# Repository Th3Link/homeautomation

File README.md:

# homeautomation

Components for a CAN-bus home-automation system: relay/rollershutter/
light/button/sensor nodes on a shared CAN bus, bridged to MQTT (and from
there to openHAB or Home Assistant) by a gateway. This repository holds
the hardware (KiCad), mechanics (3D-printable enclosures), and firmware
for the whole system.

**Start here:** [`docs/index.md`](docs/index.md) — the full documentation
index (requirements, architecture decisions, protocol specs), also built
into every crate's `cargo doc` output and published to GitHub Pages.

## Software

The firmware is Rust (`#![no_std]`, [embassy](https://embassy.dev/) async,
[esp-hal](https://github.com/esp-rs/esp-hal)), organized as one Cargo
workspace under `software/`:

- [`common-core`](software/common-core) / [`common-hardware`](software/common-hardware)
  — CAN wire-format types and ESP32 hardware-support helpers shared by
  both firmware lines.
- [`gateway-core`](software/gateway-core) / [`gateway-hardware`](software/gateway-hardware)
  — the CAN↔MQTT bridge: web config UI, `/control.json` RPC, self- and
  CAN-bus OTA update, over wired Ethernet (DHCPv4 + SLAAC, no WiFi).
- [`cancomponents-core`](software/cancomponents-core) / [`cancomponents-hardware`](software/cancomponents-hardware)
  — the node firmware living on the bus: relays, rollershutters, buttons,
  lights.
- [`tools/mqtt-log-reader`](software/tools/mqtt-log-reader) — a small
  Python tool for reading back the gateway's MQTT log/debug topics.
- [`sim/`](software/sim) — `./sim up`: the unchanged gateway and node
  firmware in QEMU, several gateways with their nodes on virtual CAN buses;
  press buttons, set what the sensors measure, watch relays and frames, in
  a TUI, from Python scripts or in pytest.
- [`legacy/`](software/legacy) — the original C++/ESP-IDF implementation,
  kept for reference. No longer built by CI.

### Building

The `*-core` crates are hardware-independent and build/test on any
machine with stable Rust:

```bash
cargo test -p gateway-core -p cancomponents-core -p common-core
```

The `*-hardware` crates target Xtensa (ESP32) and need Espressif's Rust
toolchain fork, installed via [`espup`](https://github.com/esp-rs/espup):

```bash
cargo install espup
espup install
source "$HOME/export-esp.sh"   # needed once per new shell
```

Then, from a `*-hardware` crate directory (e.g. `software/gateway-hardware/`):

```bash
cargo run --release
```

`cargo run` flashes over USB serial and opens a monitor, via `espflash`
(configured as each crate's custom runner in its own `.cargo/config.toml`).

## Hardware

### Relais

Disclaimer: if you put mains voltage on a relais board, make sure you
know what you are doing. These components are experimental and you are in
charge of your own actions. Be safe — if you're unsure, get an expert or
leave it.

Three PCBs, one shared firmware, to switch power on and off:

- **Solid-state relais (SSR)** — mains voltage only (~230V @ 50-60Hz), up
  to 1A per relay, six relais sharing one 1A fuse. Be careful with
  capacitive/inductive loads; handles small rollershutters, heating
  actuators, and electro-magnetic contactors fine.
- **Regular relais** — up to 16A each, no on-board fuse (protect your own
  circuits). No arc-quenching chamber, so an electro-magnetic contactor is
  a better choice for heavy inductive loads (motors, frequency drives).
- **Rollershutter** — two cascaded relais per channel (power, then
  up/down), with software interlocking so up and down are never active
  at once.

All three use the same firmware and the same ESP32 pinning, and each has
one extension port for up to 4 additional relay or sensor boards.

### Lightswitch, sensors, CAN header/hub, UART adapter

Additional boards in `hardware/` — see each board's own KiCad project for
details; written documentation for these is still a work in progress.

## CAN bus and MQTT protocol

See [`docs/protocol-can.md`](docs/protocol-can.md) for the byte-level CAN
wire format shared by every component, and
[`software/gateway-core/docs/protocol-mqtt.md`](software/gateway-core/docs/protocol-mqtt.md)
for the gateway's MQTT topic scheme. (Extension-board channel/button
numbering conventions used by the node firmware — e.g. which CAN
`NO`/button-id ranges map to which extension address — are documented at
the node firmware level; `docs/protocol-can.md` covers the CAN frame
format itself.)

## CI

- **CI** — `cargo fmt` / `cargo clippy` for every crate, `cargo nextest`
  with coverage and an MSRV check for the `*-core` crates.
- **Docs** — `cargo doc` for every crate, published to GitHub Pages.
- **Security audit** — [`cargo-audit`](https://github.com/rustsec/rustsec)
  against the RustSec advisory database, on every dependency change and
  once daily.
- **Renovate** — automated dependency-update PRs, once daily.

`software/legacy/` (the original C++/ESP-IDF code) is no longer built by
CI — see its own `README.md` for the ESP-IDF build steps if you need to
reproduce it.

## License

GNU General Public License v3.0 (or later) — see [LICENSE](LICENSE).

This is meant to be freely buildable, flashable, and modifiable hardware
and firmware. GPLv3 was chosen deliberately: its copyleft means anything
built on this stays open, and its Section 6 "Installation Information"
requirement means anyone who conveys a modified version as part of a
physical product also has to provide what's needed to install your own
modified firmware on it — nobody gets to lock you out of hardware you own.
All schematics, layouts, mechanics, tools, and software are provided so
you can fix things yourself rather than throwing them away.

## Contribution

Feel free to report issues or open a pull request.

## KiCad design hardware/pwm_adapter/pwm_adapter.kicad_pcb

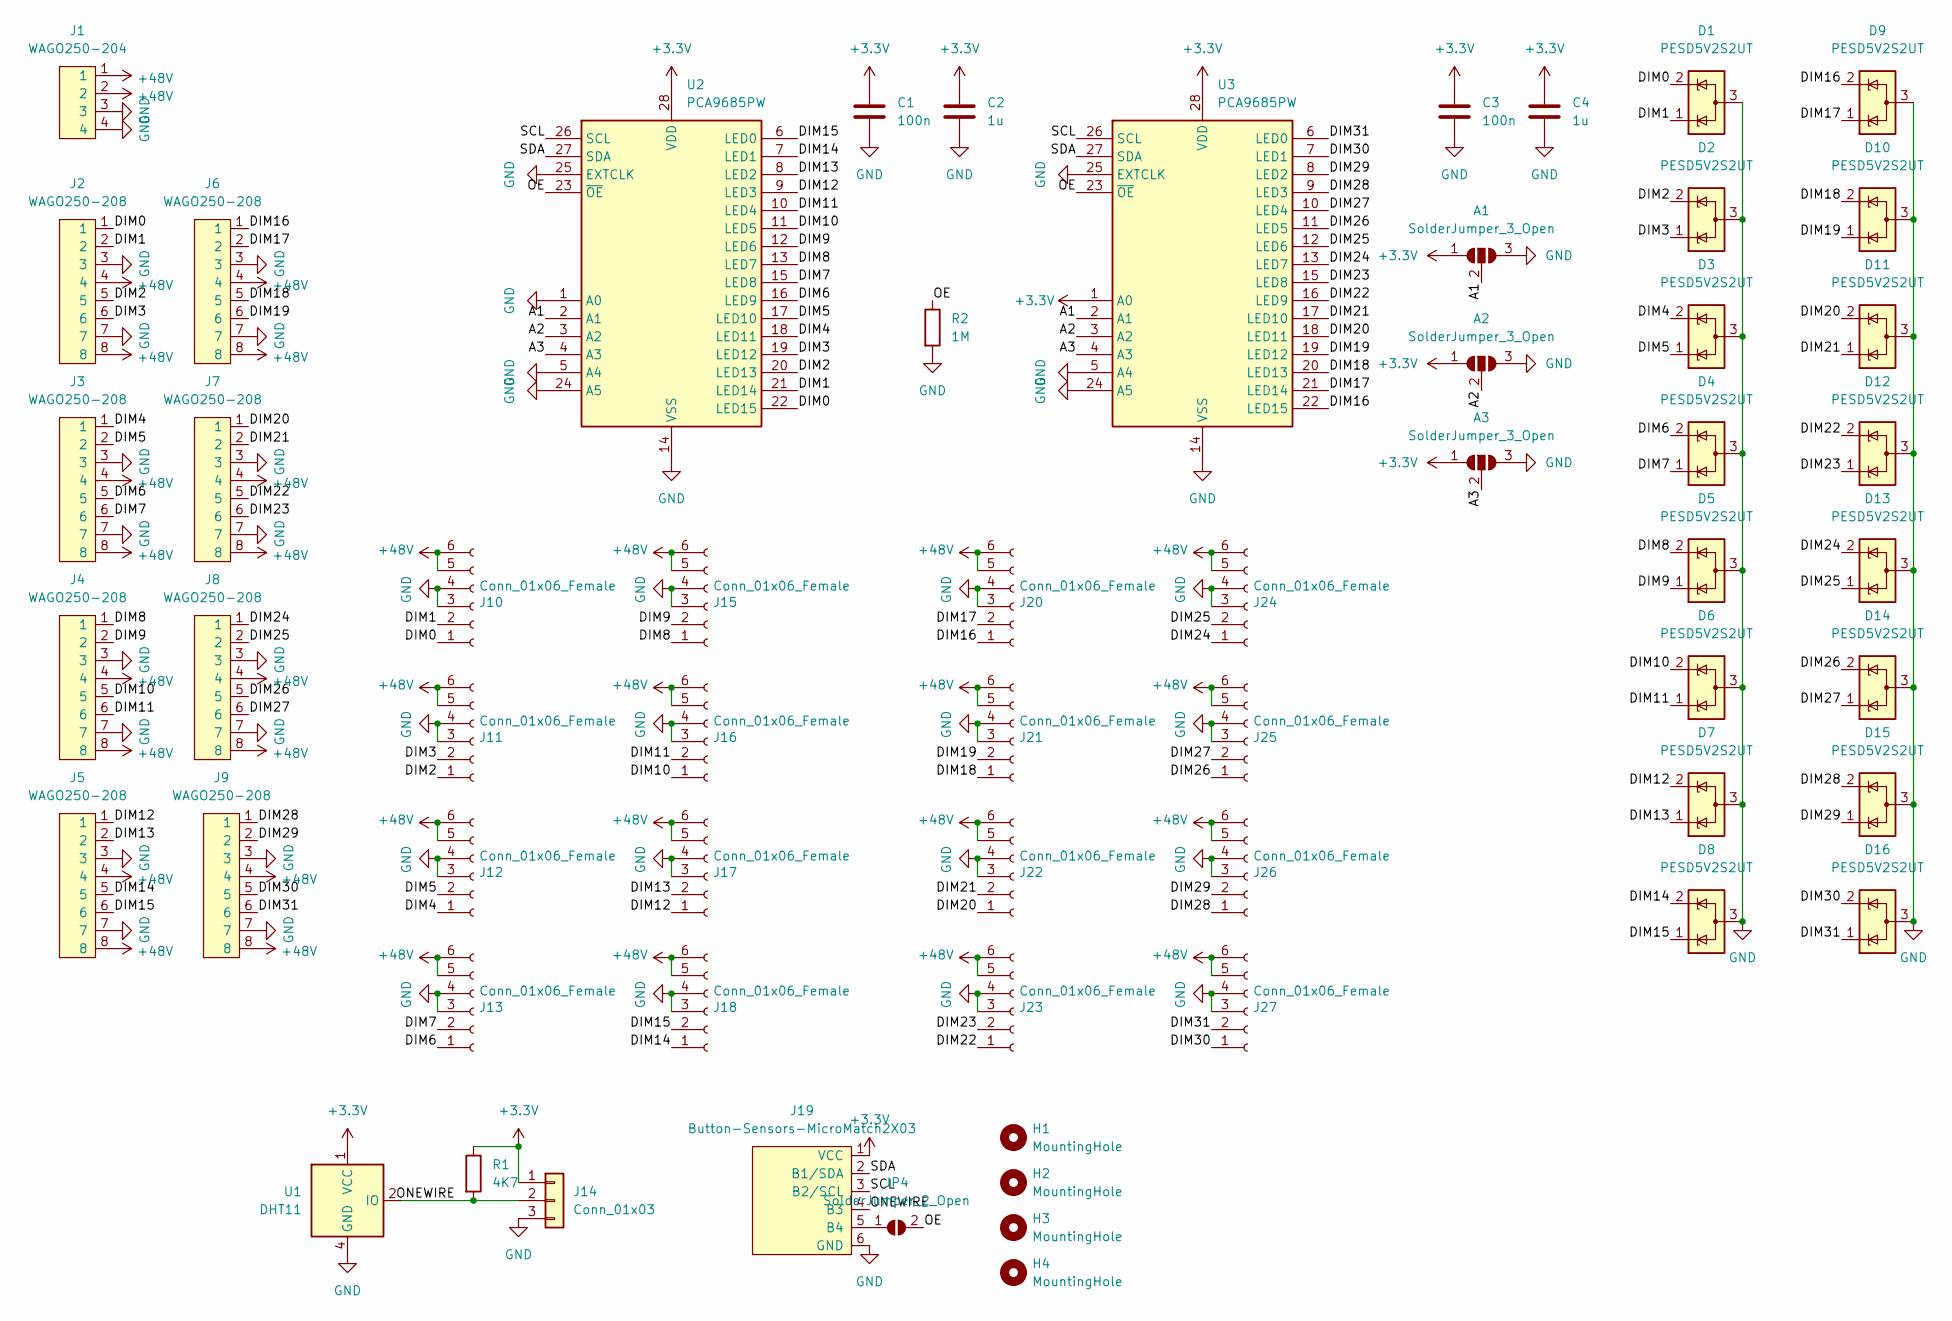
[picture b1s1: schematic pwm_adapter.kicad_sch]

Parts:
A1, A2, A3: SolderJumper_3_Open; SolderJumper-3_P1.3mm_Open_RoundedPad1.0x1.5mm
C1, C3: 100n; C_0603_1608Metric_Pad1.08x0.95mm_HandSolder
C2, C4: 1u; C_0603_1608Metric_Pad1.08x0.95mm_HandSolder
D1, D2, D3, D4, D5, D6, D7, D8, D9, D10, D11, D12, D13, D14, D15, D16: PESD5V2S2UT; SOT-23
H1, H2, H3, H4: MountingHole; MountingHole_4.3mm_M4_DIN965
J1: WAGO250-204
J2, J3, J4, J5, J6, J7, J8, J9: WAGO250-208
J10, J11, J12, J13, J15, J16, J17, J18, J20, J21, J22, J23, J24, J25, J26, J27: Conn_01x06_Female; 02x03MicroMatch
J14: Conn_01x03; PinHeader_1x03_P2.54mm_Vertical
J19: Button-Sensors-MicroMatch2X03; 02x03MicroMatch
JP4: SolderJumper_2_Open; SolderJumper-2_P1.3mm_Open_RoundedPad1.0x1.5mm
R1: 4K7; R_0603_1608Metric_Pad0.98x0.95mm_HandSolder
R2: 1M; R_0603_1608Metric_Pad0.98x0.95mm_HandSolder
U1: DHT11; Aosong_DHT11_5.5x12.0_P2.54mm
U2, U3: PCA9685PW; TSSOP-28_4.4x9.7mm_P0.65mm

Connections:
+3.3V: A1.1 (A), A2.1 (A), A3.1 (A), C1.1, C2.1, C3.1, C4.1, J14.1, J19.1 (VCC), R1.1, U1.1 (VCC), U2.28 (VDD), U3.1 (A0), U3.28 (VDD)
+48V: J1.1, J1.2, J2.4, J2.8, J3.4, J3.8, J4.4, J4.8, J5.4, J5.8, J6.4, J6.8, J7.4, J7.8, J8.4, J8.8, J9.4, J9.8, J10.5, J10.6, J11.5, J11.6, J12.5, J12.6, J13.5, J13.6, J15.5, J15.6, J16.5, J16.6, J17.5, J17.6, J18.5, J18.6, J20.5, J20.6, J21.5, J21.6, J22.5, J22.6, J23.5, J23.6, J24.5, J24.6, J25.5, J25.6, J26.5, J26.6, J27.5, J27.6
/A1: A1.2 (C), U2.2 (A1), U3.2 (A1)
/A2: A2.2 (C), U2.3 (A2), U3.3 (A2)
/A3: A3.2 (C), U2.4 (A3), U3.4 (A3)
/DIM0: D1.2 (K), J2.1, J10.1, U2.22 (LED15)
/DIM1: D1.1 (K), J2.2, J10.2, U2.21 (LED14)
/DIM2: D2.2 (K), J2.5, J11.1, U2.20 (LED13)
/DIM3: D2.1 (K), J2.6, J11.2, U2.19 (LED12)
/DIM4: D3.2 (K), J3.1, J12.1, U2.18 (LED11)
/DIM5: D3.1 (K), J3.2, J12.2, U2.17 (LED10)
/DIM6: D4.2 (K), J3.5, J13.1, U2.16 (LED9)
/DIM7: D4.1 (K), J3.6, J13.2, U2.15 (LED8)
/DIM8: D5.2 (K), J4.1, J15.1, U2.13 (LED7)
/DIM9: D5.1 (K), J4.2, J15.2, U2.12 (LED6)
/DIM10: D6.2 (K), J4.5, J16.1, U2.11 (LED5)
/DIM11: D6.1 (K), J4.6, J16.2, U2.10 (LED4)
/DIM12: D7.2 (K), J5.1, J17.1, U2.9 (LED3)
/DIM13: D7.1 (K), J5.2, J17.2, U2.8 (LED2)
/DIM14: D8.2 (K), J5.5, J18.1, U2.7 (LED1)
/DIM15: D8.1 (K), J5.6, J18.2, U2.6 (LED0)
/DIM16: D9.2 (K), J6.1, J20.1, U3.22 (LED15)
/DIM17: D9.1 (K), J6.2, J20.2, U3.21 (LED14)
/DIM18: D10.2 (K), J6.5, J21.1, U3.20 (LED13)
/DIM19: D10.1 (K), J6.6, J21.2, U3.19 (LED12)
/DIM20: D11.2 (K), J7.1, J22.1, U3.18 (LED11)
/DIM21: D11.1 (K), J7.2, J22.2, U3.17 (LED10)
/DIM22: D12.2 (K), J7.5, J23.1, U3.16 (LED9)
/DIM23: D12.1 (K), J7.6, J23.2, U3.15 (LED8)
/DIM24: D13.2 (K), J8.1, J24.1, U3.13 (LED7)
/DIM25: D13.1 (K), J8.2, J24.2, U3.12 (LED6)
/DIM26: D14.2 (K), J8.5, J25.1, U3.11 (LED5)
/DIM27: D14.1 (K), J8.6, J25.2, U3.10 (LED4)
/DIM28: D15.2 (K), J9.1, J26.1, U3.9 (LED3)
/DIM29: D15.1 (K), J9.2, J26.2, U3.8 (LED2)
/DIM30: D16.2 (K), J9.5, J27.1, U3.7 (LED1)
/DIM31: D16.1 (K), J9.6, J27.2, U3.6 (LED0)
/OE: JP4.2 (B), R2.1, U2.23 (~OE), U3.23 (~OE)
/ONEWIRE: J14.2, J19.4 (B3), R1.2, U1.2 (IO)
/SCL: J19.3 (B2/SCL), U2.26 (SCL), U3.26 (SCL)
/SDA: J19.2 (B1/SDA), U2.27 (SDA), U3.27 (SDA)
GND: A1.3 (B), A2.3 (B), A3.3 (B), C1.2, C2.2, C3.2, C4.2, D1.3 (A), D2.3 (A), D3.3 (A), D4.3 (A), D5.3 (A), D6.3 (A), D7.3 (A), D8.3 (A), D9.3 (A), D10.3 (A), D11.3 (A), D12.3 (A), D13.3 (A), D14.3 (A), D15.3 (A), D16.3 (A), J1.3, J1.4, J2.3, J2.7, J3.3, J3.7, J4.3, J4.7, J5.3, J5.7, J6.3, J6.7, J7.3, J7.7, J8.3, J8.7, J9.3, J9.7, J10.3, J10.4, J11.3, J11.4, J12.3, J12.4, J13.3, J13.4, J14.3, J15.3, J15.4, J16.3, J16.4, J17.3, J17.4, J18.3, J18.4, J19.6 (GND), J20.3, J20.4, J21.3, J21.4, J22.3, J22.4, J23.3, J23.4, J24.3, J24.4, J25.3, J25.4, J26.3, J26.4, J27.3, J27.4, R2.2, U1.4 (GND), U2.1 (A0), U2.5 (A4), U2.14 (VSS), U2.24 (A5), U2.25 (EXTCLK), U3.5 (A4), U3.14 (VSS), U3.24 (A5), U3.25 (EXTCLK)
unnamed: J19.5 (B4), JP4.1 (A)

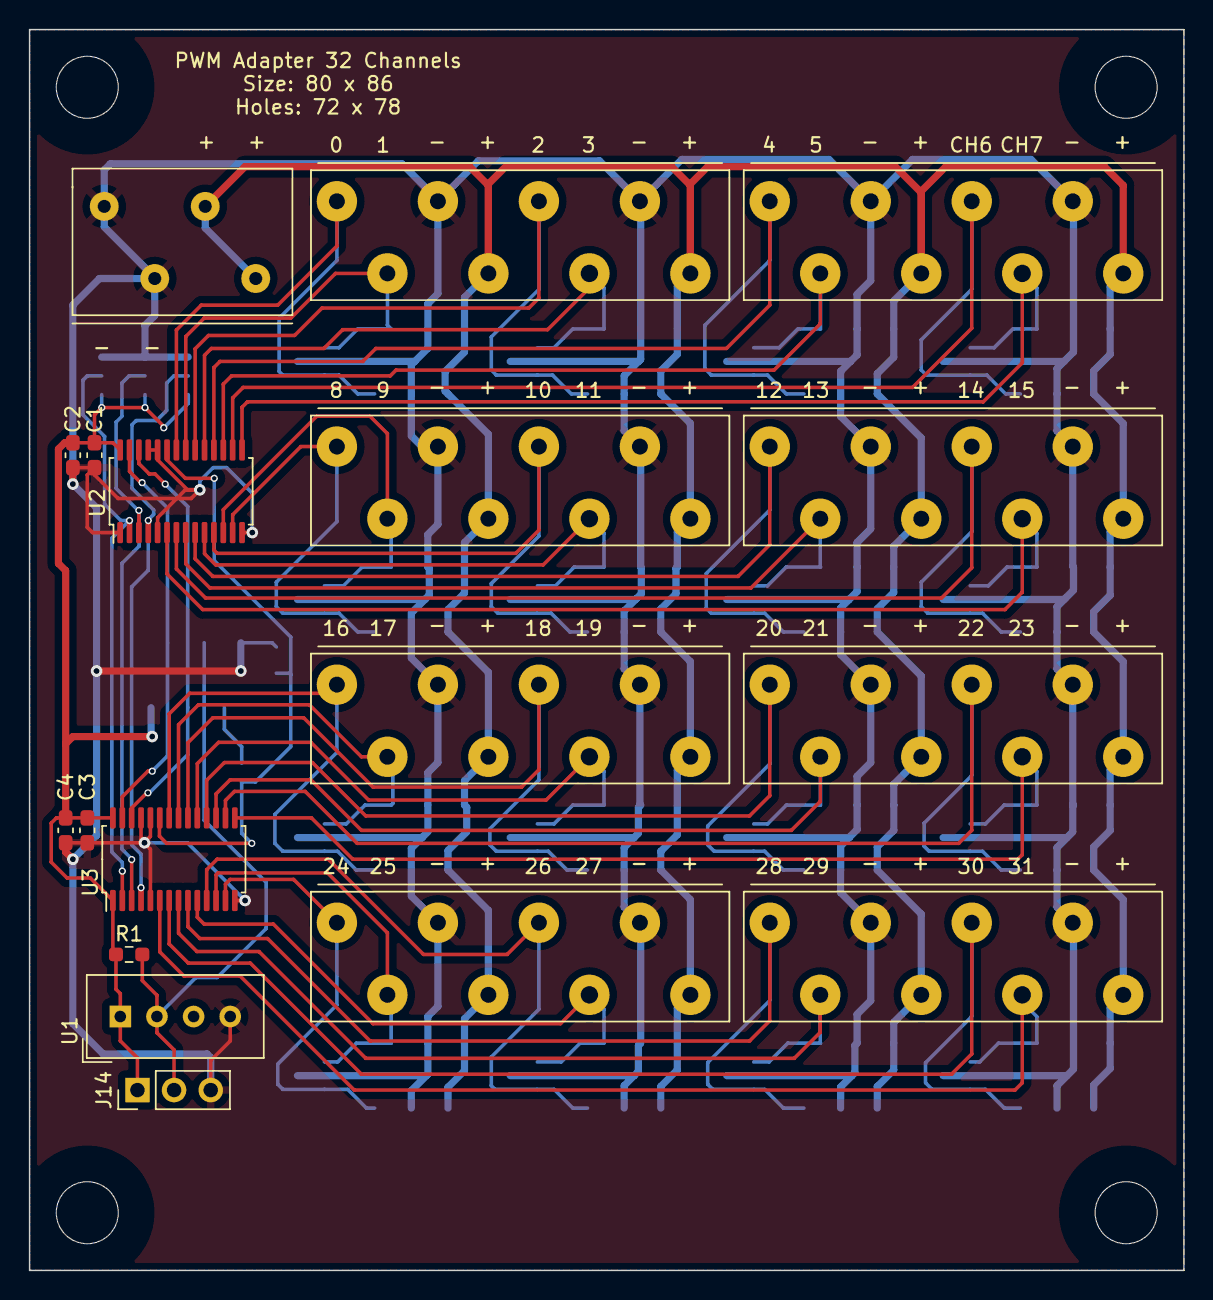
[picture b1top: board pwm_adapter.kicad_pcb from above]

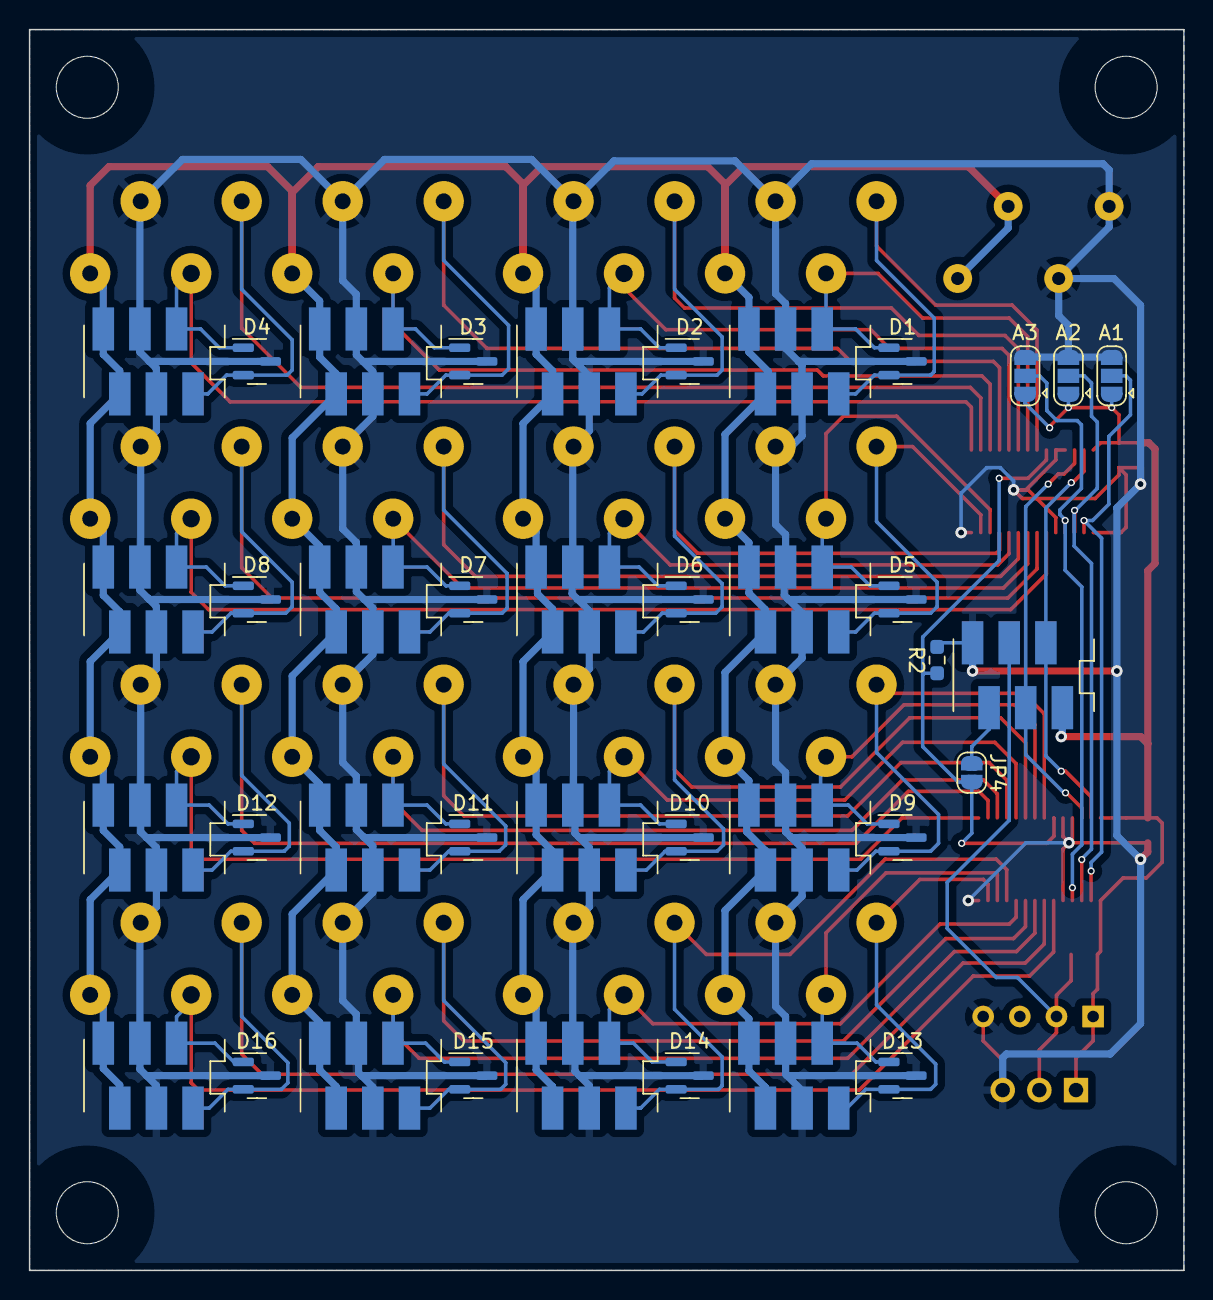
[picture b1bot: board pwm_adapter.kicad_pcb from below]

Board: 2 copper layers, 80.0 x 86.0 mm, 60 parts (38 on the bottom side), 43 nets.

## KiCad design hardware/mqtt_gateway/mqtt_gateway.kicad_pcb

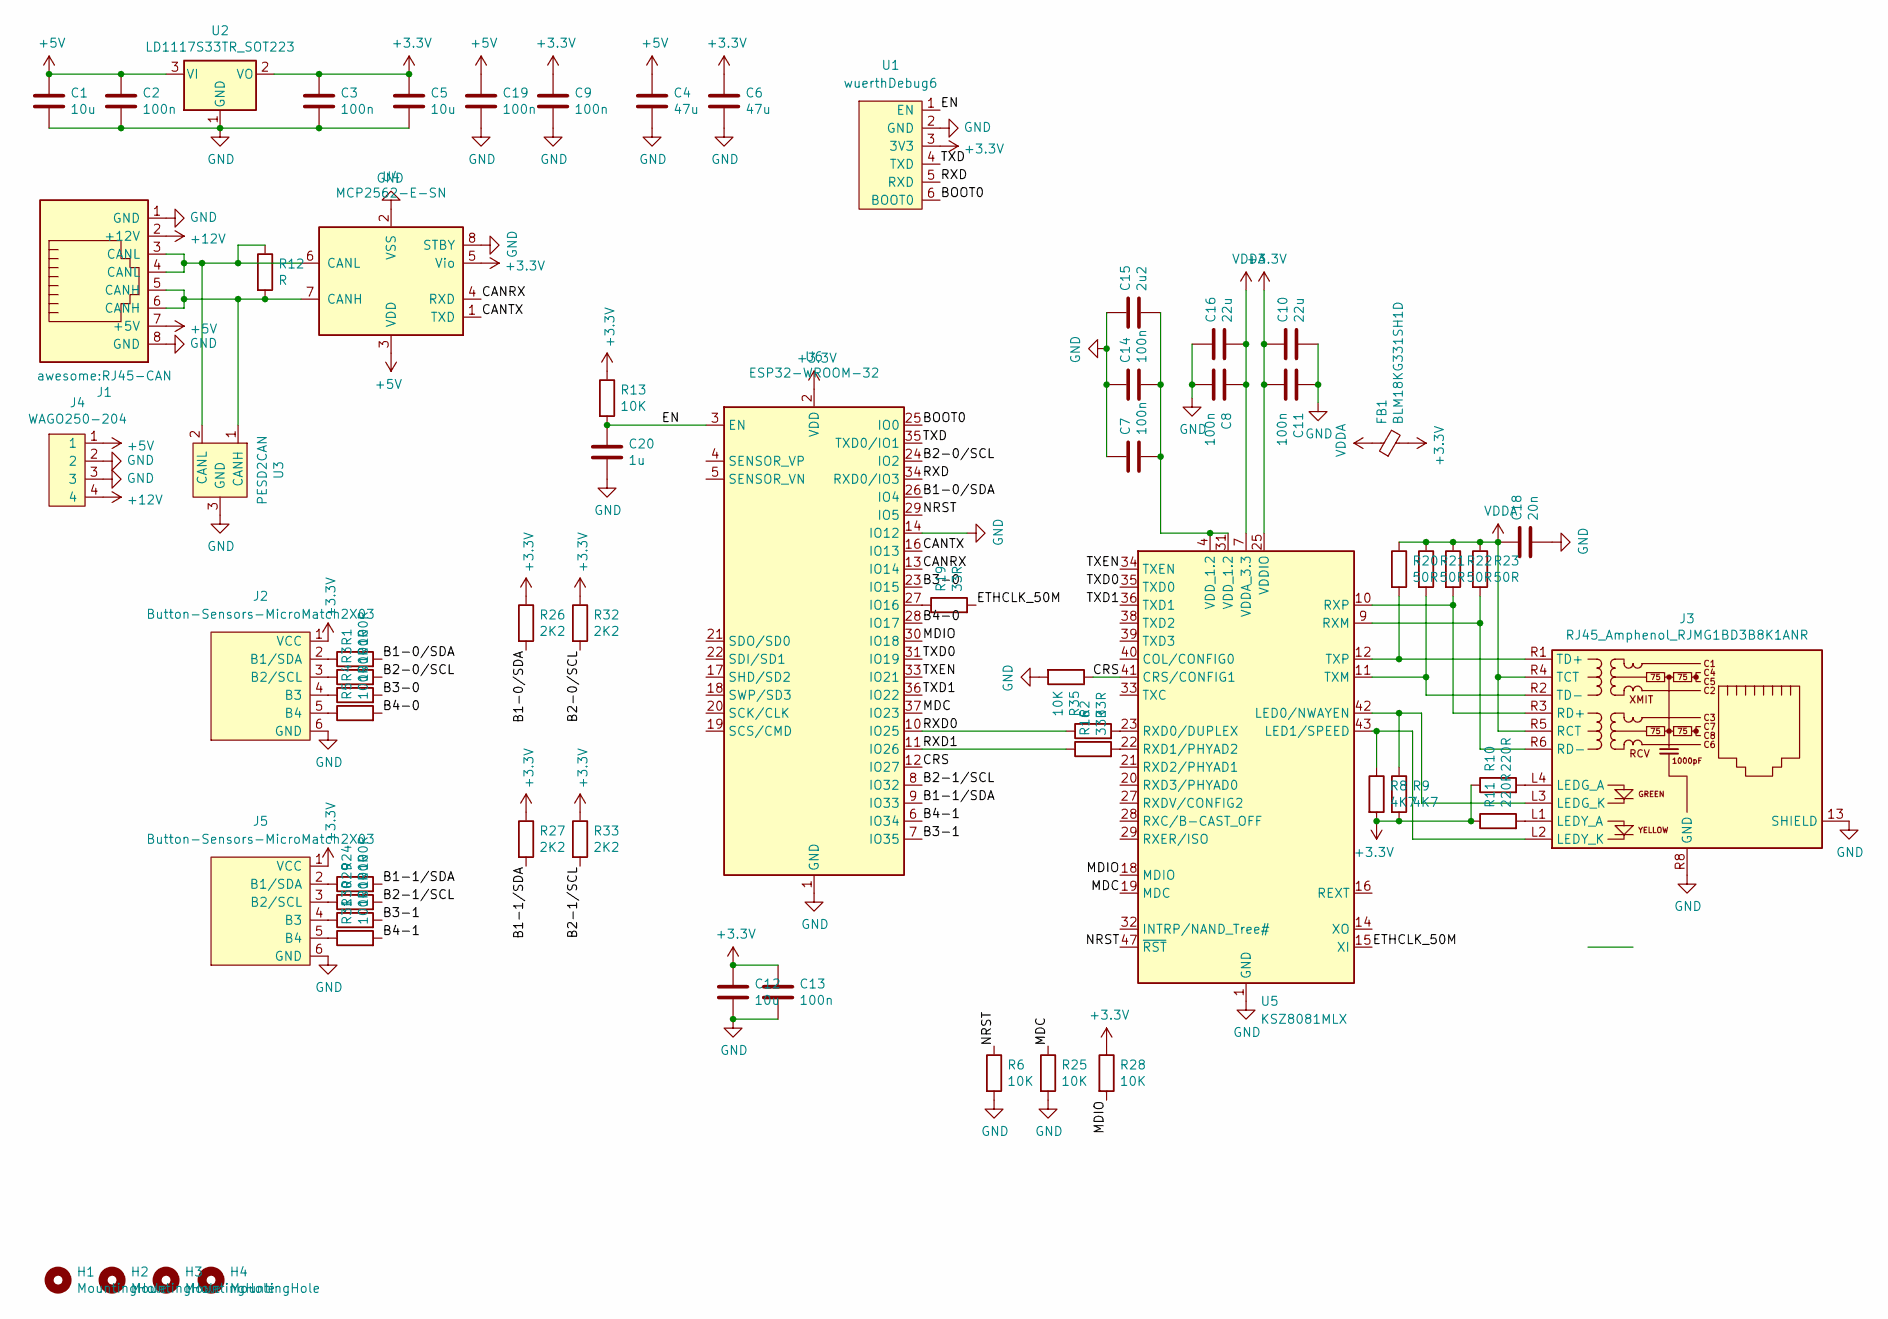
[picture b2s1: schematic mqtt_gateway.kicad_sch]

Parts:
C1, C5, C12: 10u; C_0603_1608Metric_Pad1.08x0.95mm_HandSolder
C2, C3, C7, C8, C9, C11, C13, C14, C19: 100n; C_0603_1608Metric_Pad1.08x0.95mm_HandSolder
C4, C6: 47u; C_0805_2012Metric_Pad1.18x1.45mm_HandSolder
C10, C16: 22u; C_0805_2012Metric_Pad1.18x1.45mm_HandSolder
C15: 2u2; C_0603_1608Metric_Pad1.08x0.95mm_HandSolder
C18: 20n; C_0603_1608Metric_Pad1.08x0.95mm_HandSolder
C20: 1u; C_0603_1608Metric_Pad1.08x0.95mm_HandSolder
FB1: BLM18KG331SH1D; C_0603_1608Metric_Pad1.08x0.95mm_HandSolder
H1, H2, H3, H4: MountingHole; MountingHole_3.2mm_M3
J1: awesome:RJ45-CAN; RJ45_OST_PJ012-8P8CX_Vertical
J2, J5: Button-Sensors-MicroMatch2X03; 02x03MicroMatch
J3: RJ45_Amphenol_RJMG1BD3B8K1ANR
J4: WAGO250-204
R1, R3, R4, R5, R24, R29, R30, R31: 100R; R_0603_1608Metric_Pad0.98x0.95mm_HandSolder
R2, R16, R19: 33R; R_0603_1608Metric_Pad0.98x0.95mm_HandSolder
R6, R13, R25, R28, R35: 10K; R_0603_1608Metric_Pad0.98x0.95mm_HandSolder
R8, R9: 4K7; R_0603_1608Metric_Pad0.98x0.95mm_HandSolder
R10, R11: 220R; R_0603_1608Metric_Pad0.98x0.95mm_HandSolder
R12: R; R_0603_1608Metric_Pad0.98x0.95mm_HandSolder
R20, R21, R22, R23: 50R; R_0603_1608Metric_Pad0.98x0.95mm_HandSolder
R26, R27, R32, R33: 2K2; R_0603_1608Metric_Pad0.98x0.95mm_HandSolder
U1: wuerthDebug6
U2: LD1117S33TR_SOT223; SOT-223-3_TabPin2
U3: PESD2CAN; SOT-23
U4: MCP2562-E-SN; SOIC-8_3.9x4.9mm_P1.27mm
U5: KSZ8081MLX; LQFP-48_7x7mm_P0.5mm
U6: ESP32-WROOM-32

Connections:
+3.3V: C3.1, C5.1, C6.1, C9.1, C10.1, C11.2, C12.1, C13.1, FB1.2, J2.1 (VCC), J5.1 (VCC), R8.2, R9.2, R10.1, R11.1, R13.1, R26.1, R27.1, R28.1, R32.1, R33.1, U1.3 (3V3), U2.2 (VO), U4.5 (Vio), U5.25 (VDDIO), U6.2 (VDD)
+5V: C1.1, C2.1, C4.1, C19.1, J1.7 (+5V), J4.1, U2.3 (VI), U4.3 (VDD)
+12V: J1.2 (+12V), J4.4
/B1-0/SDA: R1.2, R26.2, U6.26 (IO4)
/B1-1/SDA: R24.2, R27.2, U6.9 (IO33)
/B2-0/SCL: R3.2, R32.2, U6.24 (IO2)
/B2-1/SCL: R29.2, R33.2, U6.8 (IO32)
/B3-0: R4.2, U6.23 (IO15)
/B3-1: R30.2, U6.7 (IO35)
/B4-0: R5.2, U6.28 (IO17)
/B4-1: R31.2, U6.6 (IO34)
/BOOT0: U1.6 (BOOT0), U6.25 (IO0)
/CANRX: U4.4 (RXD), U6.13 (IO14)
/CANTX: U4.1 (TXD), U6.16 (IO13)
/CRS: R35.1, U5.41 (CRS/CONFIG1), U6.12 (IO27)
/EN: C20.1, R13.2, U1.1 (EN), U6.3 (EN)
/ETHCLK_50M: R19.2, U5.15 (XI)
/MDC: R25.1, U5.19 (MDC), U6.37 (IO23)
/MDIO: R28.2, U5.18 (MDIO), U6.30 (IO18)
/NRST: R6.1, U5.47 (~RST), U6.29 (IO5)
/RXD: U1.5 (RXD), U6.34 (RXD0/IO3)
/RXD0: R2.1, U6.10 (IO25)
/RXD1: R16.1, U6.11 (IO26)
/TXD: U1.4 (TXD), U6.35 (TXD0/IO1)
/TXD0: U5.35 (TXD0), U6.31 (IO19)
/TXD1: U5.36 (TXD1), U6.36 (IO22)
/TXEN: U5.34 (TXEN), U6.33 (IO21)
GND: C1.2, C2.2, C3.2, C4.2, C5.2, C6.2, C7.1, C8.2, C9.2, C10.2, C11.1, C12.2, C13.2, C14.1, C15.1, C16.1, C18.2, C19.2, C20.2, J1.1 (GND), J1.8 (GND), J2.6 (GND), J3.13 (SHIELD), J3.R8 (GND), J4.2, J4.3, J5.6 (GND), R6.2, R25.2, R35.2, U1.2 (GND), U2.1 (GND), U3.3 (GND), U4.2 (VSS), U4.8 (STBY), U5.1 (GND), U5.2 (GND), U5.3 (GND), U5.13 (GND), U5.17 (GND), U5.24 (GND), U5.30 (GND), U5.37 (GND), U6.1 (GND), U6.14 (IO12), U6.15 (GND), U6.38 (GND), U6.39 (GND)
unnamed: C7.2, C14.2, C15.2, U5.4 (VDD_1.2), U5.31 (VDD_1.2)
unnamed: J2.2 (B1/SDA), R1.1
unnamed: J2.3 (B2/SCL), R3.1
unnamed: J2.4 (B3), R4.1
unnamed: J2.5 (B4), R5.1
unnamed: J3.L4 (LEDG_A), R10.2
unnamed: J3.L3 (LEDG_K), R9.1, U5.42 (LED0/NWAYEN)
unnamed: J3.L1 (LEDY_A), R11.2
unnamed: J3.L2 (LEDY_K), R8.1, U5.43 (LED1/SPEED)
unnamed: J3.R3 (RD+), R22.2, U5.10 (RXP)
unnamed: J3.R6 (RD-), R23.2, U5.9 (RXM)
unnamed: J3.R1 (TD+), R20.2, U5.12 (TXP)
unnamed: J3.R2 (TD-), R21.2, U5.11 (TXM)
unnamed: J5.2 (B1/SDA), R24.1
unnamed: J5.3 (B2/SCL), R29.1
unnamed: J5.4 (B3), R30.1
unnamed: J5.5 (B4), R31.1
unnamed: J1.5 (CANH), J1.6 (CANH), R12.2, U3.1 (CANH), U4.7 (CANH)
unnamed: J1.3 (CANL), J1.4 (CANL), R12.1, U3.2 (CANL), U4.6 (CANL)
unnamed: R2.2, U5.23 (RXD0/DUPLEX)
unnamed: R16.2, U5.22 (RXD1/PHYAD2)
unnamed: R19.1, U6.27 (IO16)
VDDA: C8.1, C16.2, C18.1, FB1.1, J3.R4 (TCT), J3.R5 (RCT), R20.1, R21.1, R22.1, R23.1, U5.7 (VDDA_3.3)

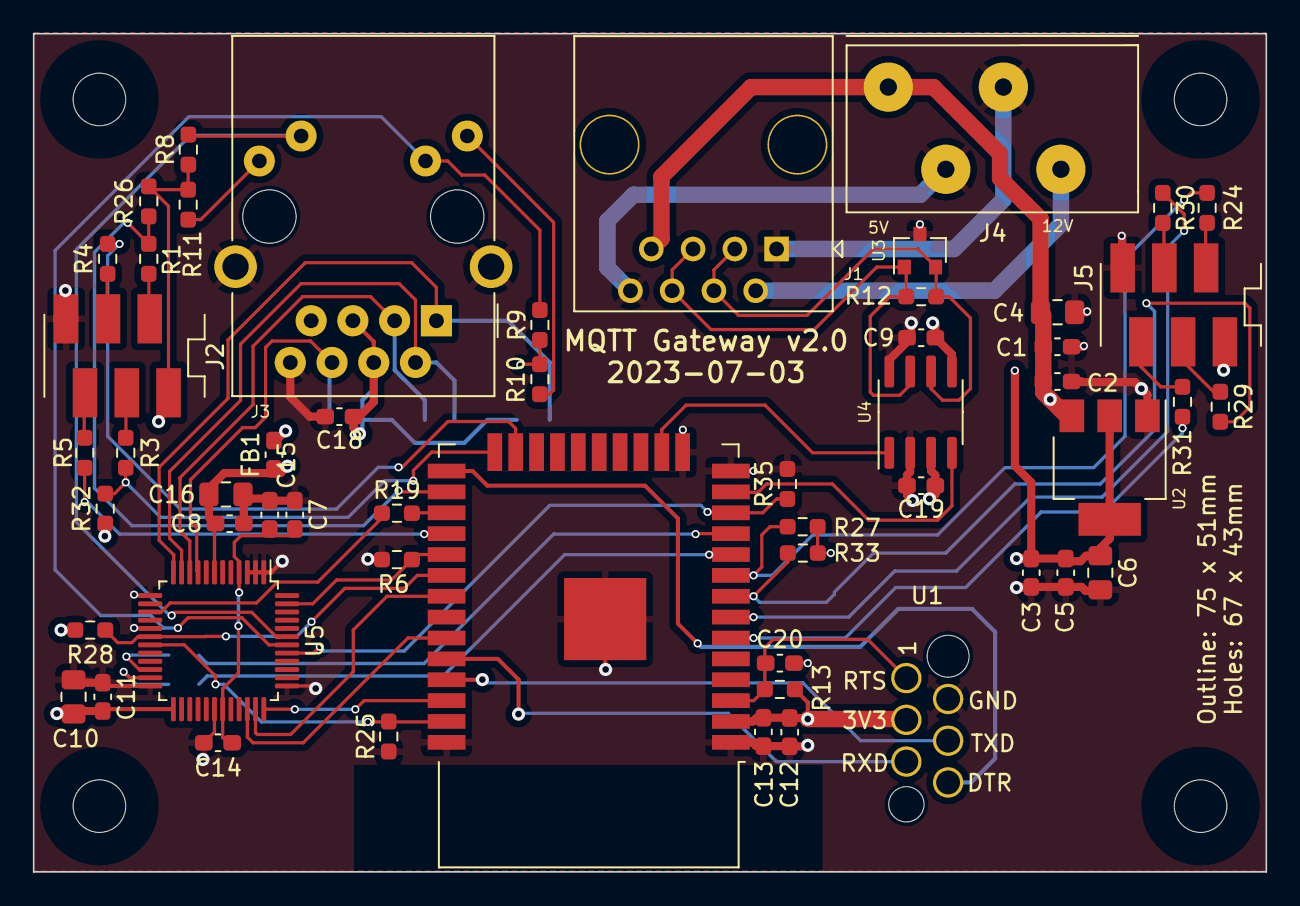
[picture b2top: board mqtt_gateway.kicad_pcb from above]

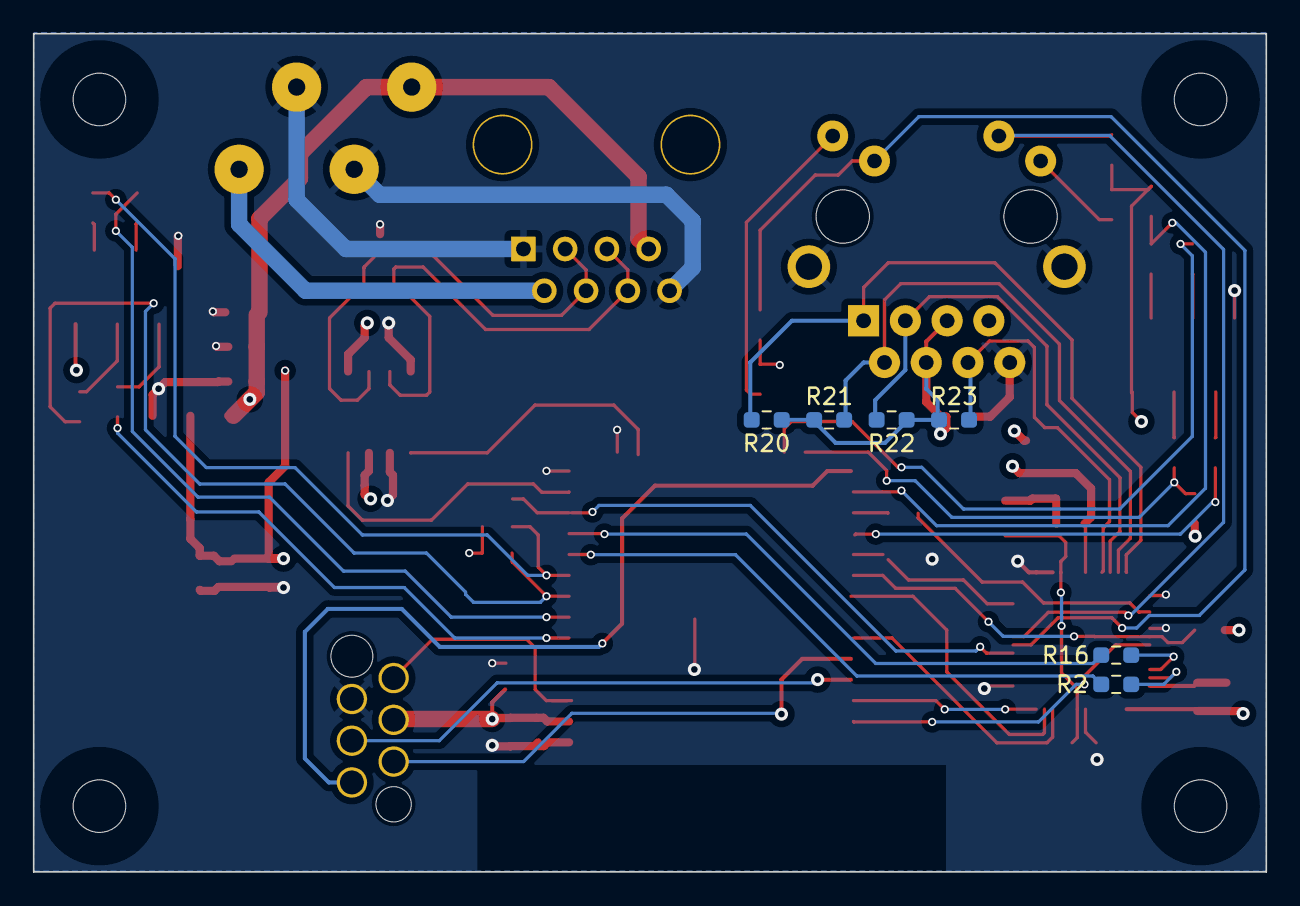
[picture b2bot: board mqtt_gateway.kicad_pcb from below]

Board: 4 copper layers, 75.0 x 51.0 mm, 64 parts (6 on the bottom side), 51 nets.

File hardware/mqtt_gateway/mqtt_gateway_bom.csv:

"Id";"Designator";"Footprint";"Quantity";"Designation";"Supplier and ref";
1;"C16,C10";"C_0805_2012Metric_Pad1.18x1.45mm_HandSolder";2;"22u";;;
2;"C7,C14,C11,C8,C2,C3,C9,C13,C19";"C_0603_1608Metric_Pad1.08x0.95mm_HandSolder";9;"100n";;;
3;"U6";"ESP32-WROOM-32";1;"ESP32-WROOM-32";;;
4;"R35,R6,R13,R28,R25";"R_0603_1608Metric_Pad0.98x0.95mm_HandSolder";5;"10K";;;
5;"U5";"LQFP-48_7x7mm_P0.5mm";1;"KSZ8081MLX";;;
6;"R16,R2,R19";"R_0603_1608Metric_Pad0.98x0.95mm_HandSolder";3;"33R";;;
7;"C15";"C_0603_1608Metric_Pad1.08x0.95mm_HandSolder";1;"2u2";;;
8;"C1,C12,C5";"C_0603_1608Metric_Pad1.08x0.95mm_HandSolder";3;"10u";;;
9;"C18";"C_0603_1608Metric_Pad1.08x0.95mm_HandSolder";1;"20n";;;
10;"FB1";"C_0603_1608Metric_Pad1.08x0.95mm_HandSolder";1;"BLM18KG331SH1D";;;
11;"J1";"RJ45_OST_PJ012-8P8CX_Vertical";1;"awesome:RJ45-CAN";;;
12;"J3";"RJ45_Amphenol_RJMG1BD3B8K1ANR";1;"RJ45_Amphenol_RJMG1BD3B8K1ANR";;;
13;"R8,R9";"R_0603_1608Metric_Pad0.98x0.95mm_HandSolder";2;"4K7";;;
14;"R10,R11";"R_0603_1608Metric_Pad0.98x0.95mm_HandSolder";2;"220R";;;
15;"U2";"SOT-223-3_TabPin2";1;"LD1117S33TR_SOT223";;;
16;"U3";"SOT-23";1;"PESD2CAN";;;
17;"U4";"SOIC-8_3.9x4.9mm_P1.27mm";1;"MCP2562-E-SN";;;
18;"R12";"R_0603_1608Metric_Pad0.98x0.95mm_HandSolder";1;"R";;;
19;"H2,H3,H4,H1";"MountingHole_3.2mm_M3";4;"MountingHole";;;
20;"C20";"C_0603_1608Metric_Pad1.08x0.95mm_HandSolder";1;"1u";;;
21;"J4";"WAGO250-204";1;"WAGO250-204";;;
22;"C4,C6";"C_0805_2012Metric_Pad1.18x1.45mm_HandSolder";2;"47u";;;
23;"R30,R31,R29,R4,R24,R3,R1,R5";"R_0603_1608Metric_Pad0.98x0.95mm_HandSolder";8;"100R";;;
24;"R32,R27,R26,R33";"R_0603_1608Metric_Pad0.98x0.95mm_HandSolder";4;"2K2";;;
25;"J2,J5";"02x03MicroMatch";2;"Button-Sensors-MicroMatch2X03";;;
26;"U1";"wuerthDebug6";1;"wuerthDebug6";;;
27;"R20,R21,R22,R23";"R_0603_1608Metric_Pad0.98x0.95mm_HandSolder";4;"50R";;;

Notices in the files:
parts and their libraries:
Copyright 2021 Accelerated Designs. All rights reserved.
